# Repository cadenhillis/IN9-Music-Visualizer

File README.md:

# IN9-Music-Visualizer
Teensy 3.6  Based Music Visualizer utilizing the built-in audio library

11 IN9 Nixie tubes are driven thru low side BJT current sinks. Controllable thru the Teensy's PWM and powerful Audio Library.

The 12-150V boost supply is no laughing matter, by far the hardest to design -- as 11 IN9's can draw a peak of 20W. The medium power and high-voltage are quite a challenge for any electronics hobbiest.

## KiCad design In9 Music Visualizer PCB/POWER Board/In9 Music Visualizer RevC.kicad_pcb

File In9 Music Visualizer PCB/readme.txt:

This top level KiCad project is the top-level schematic with the board.

The Power Board and Signal Board sub directorys are boards separated by their sections, as the power side works better with 2oz 4 layers and the signal side only needs 2 layers and 2oz is overkill

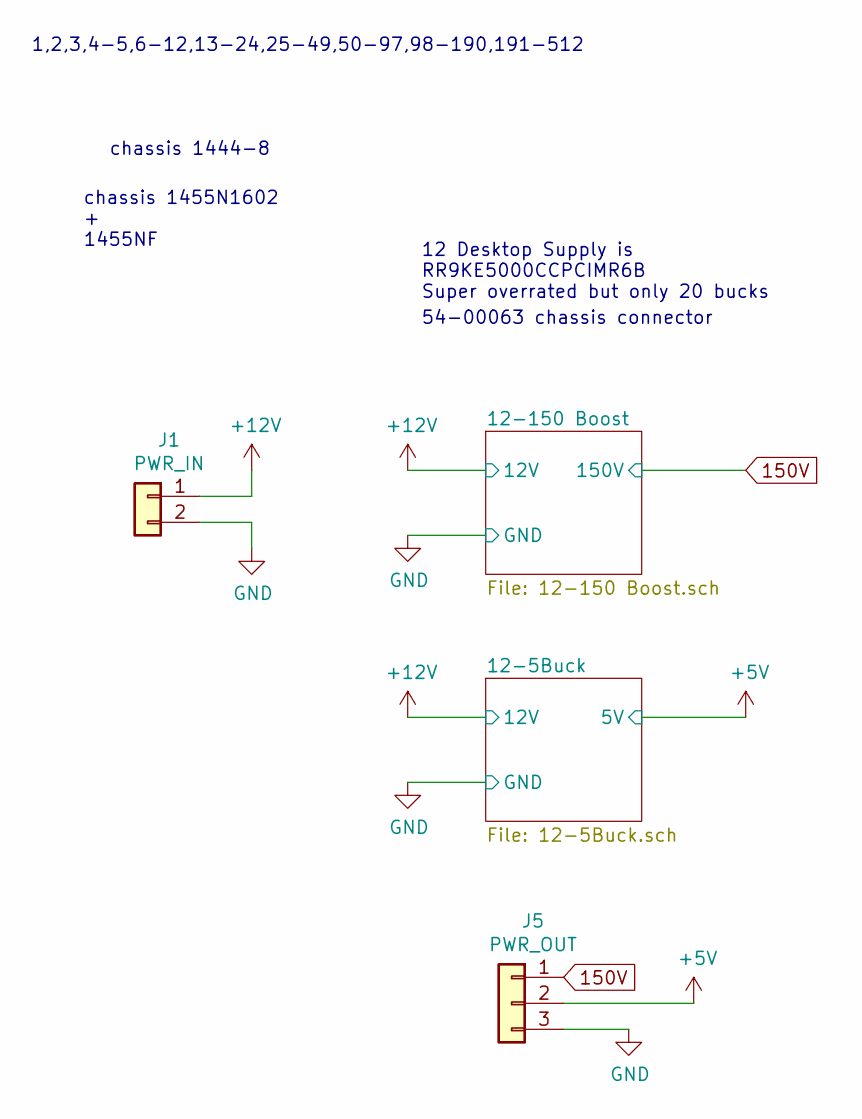
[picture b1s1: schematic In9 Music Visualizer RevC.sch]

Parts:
J1: PWR_IN; 640456-2
J5: PWR_OUT; 640456-3

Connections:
150V: J5.1; also elsewhere on the board
+5V: J5.2; also elsewhere on the board
+12V: J1.1; also elsewhere on the board
GND: J1.2, J5.3; also elsewhere on the board

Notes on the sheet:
chassis 1455N1602 + 1455NF
chassis 1444-8
54-00063 chassis connector
1,2,3,4-5,6-12,13-24,25-49,50-97,98-190,191-512
12 Desktop Supply is RR9KE5000CCPCIMR6B Super overrated but only 20 bucks

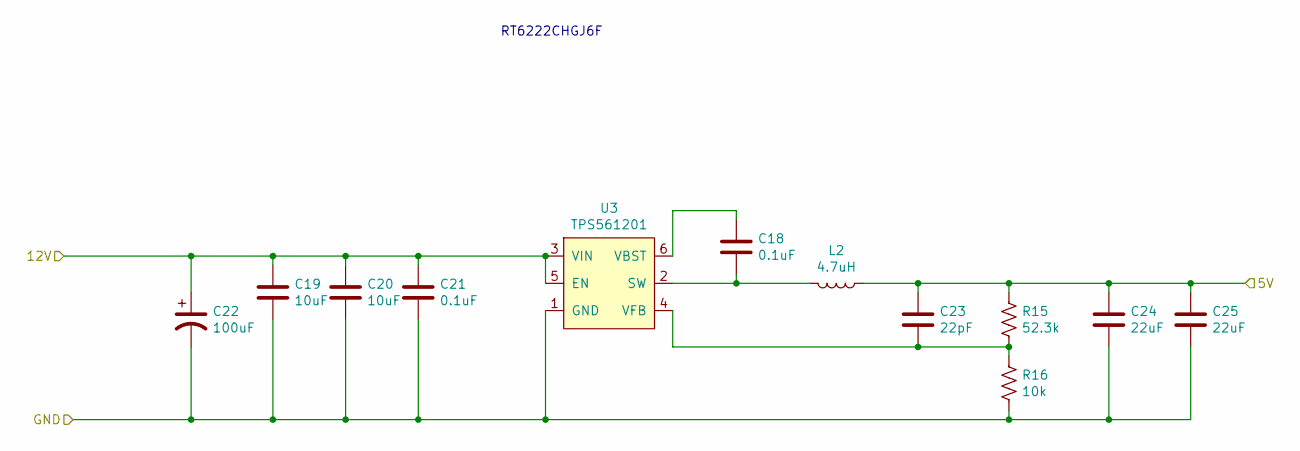
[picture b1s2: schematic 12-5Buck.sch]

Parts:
C18, C21: 0.1uF; C_0805_2012Metric_Pad1.18x1.45mm_HandSolder
C19, C20: 10uF; C_0805_2012Metric_Pad1.18x1.45mm_HandSolder
C22: 100uF; CP_Radial_D6.3mm_P2.50mm
C23: 22pF; C_0805_2012Metric_Pad1.18x1.45mm_HandSolder
C24, C25: 22uF; C_0805_2012Metric_Pad1.18x1.45mm_HandSolder
L2: 4.7uH; L_Bourns_SRN6045TA
R15: 52.3k; R_0805_2012Metric_Pad1.20x1.40mm_HandSolder
R16: 10k; R_0805_2012Metric_Pad1.20x1.40mm_HandSolder
U3: TPS561201; SOT-23-6

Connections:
+5V: C23.1, C24.1, C25.1, L2.1, R15.1; also elsewhere on the board
+12V: C19.1, C20.1, C21.1, C22.1, U3.3 (VIN), U3.5 (EN); also elsewhere on the board
GND: C19.2, C20.2, C21.2, C22.2, C24.2, C25.2, R16.2, U3.1 (GND); also elsewhere on the board
unnamed: C18.1, U3.6 (VBST)
unnamed: C18.2, L2.2, U3.2 (SW)
unnamed: C23.2, R15.2, R16.1, U3.4 (VFB)

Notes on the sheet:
RT6222CHGJ6F

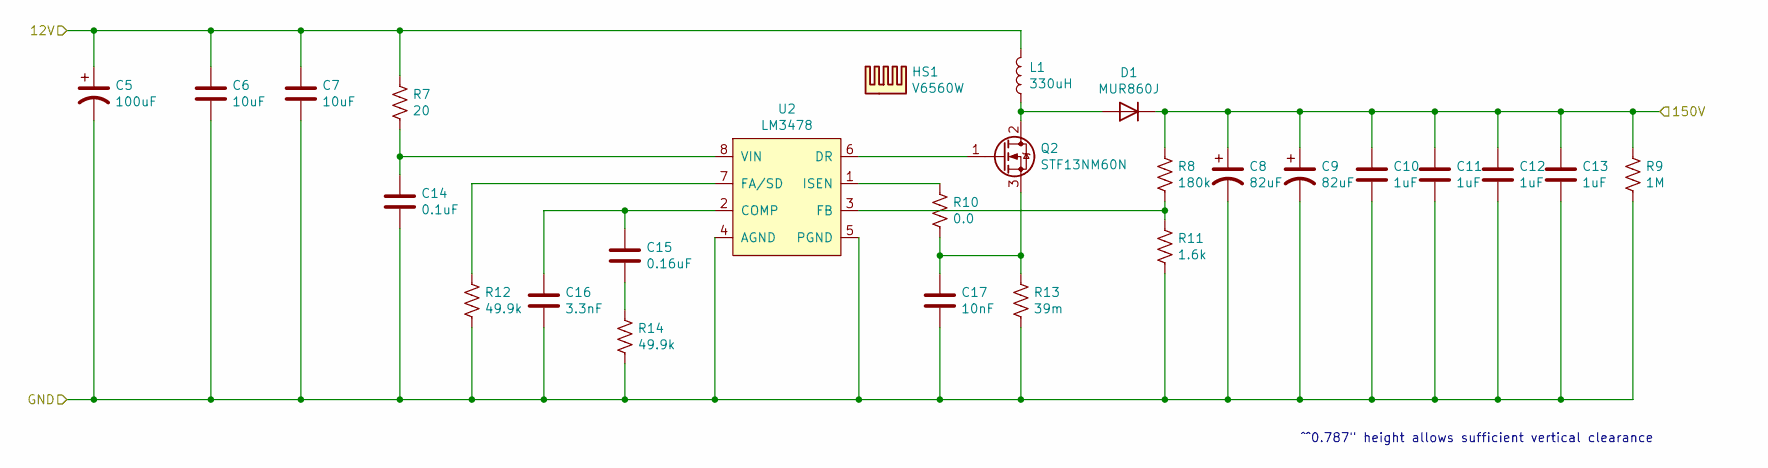
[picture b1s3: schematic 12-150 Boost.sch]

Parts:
C5: 100uF; CP_Radial_D6.3mm_P2.50mm
C6, C7: 10uF; C_0805_2012Metric_Pad1.18x1.45mm_HandSolder
C8, C9: 82uF; CP_Radial_D18.0mm_P7.50mm
C10, C11, C12, C13: 1uF; C_2220_5650Metric_Pad1.97x5.40mm_HandSolder
C14: 0.1uF; C_0805_2012Metric_Pad1.18x1.45mm_HandSolder
C15: 0.16uF; C_0805_2012Metric_Pad1.18x1.45mm_HandSolder
C16: 3.3nF; C_0805_2012Metric_Pad1.18x1.45mm_HandSolder
C17: 10nF; C_0805_2012Metric_Pad1.18x1.45mm_HandSolder
D1: MUR860J; D_SMC_Handsoldering
HS1: V6560W
L1: 330uH; L_Murata_6000B
Q2: STF13NM60N; TO-220-3_Vertical
R7: 20; R_0805_2012Metric_Pad1.20x1.40mm_HandSolder
R8: 180k; R_0805_2012Metric_Pad1.20x1.40mm_HandSolder
R9: 1M; R_0805_2012Metric_Pad1.20x1.40mm_HandSolder
R10: 0.0; R_0805_2012Metric_Pad1.20x1.40mm_HandSolder
R11: 1.6k; R_0805_2012Metric_Pad1.20x1.40mm_HandSolder
R12, R14: 49.9k; R_0805_2012Metric_Pad1.20x1.40mm_HandSolder
R13: 39m; R_1206_3216Metric_Pad1.30x1.75mm_HandSolder
U2: LM3478; SO-8_3.9x4.9mm_P1.27mm

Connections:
150V: C8.1, C9.1, C10.1, C11.1, C12.1, C13.1, D1.1 (K), R8.1, R9.1; also elsewhere on the board
+12V: C5.1, C6.1, C7.1, L1.2, R7.1; also elsewhere on the board
GND: C5.2, C6.2, C7.2, C8.2, C9.2, C10.2, C11.2, C12.2, C13.2, C14.2, C16.2, C17.2, R9.2, R11.2, R12.2, R13.2, R14.2, U2.4 (AGND), U2.5 (PGND); also elsewhere on the board
unnamed: C14.1, R7.2, U2.8 (VIN)
unnamed: C15.1, C16.1, U2.2 (COMP)
unnamed: C15.2, R14.1
unnamed: C17.1, Q2.3 (S), R10.1, R13.1
unnamed: D1.2 (A), L1.1, Q2.2 (D)
unnamed: Q2.1 (G), U2.6 (DR)
unnamed: R10.2, U2.1 (ISEN)
unnamed: R8.2, R11.1, U2.3 (FB)
unnamed: R12.1, U2.7 (FA/SD)

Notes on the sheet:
^^0.787" height allows sufficient vertical clearance

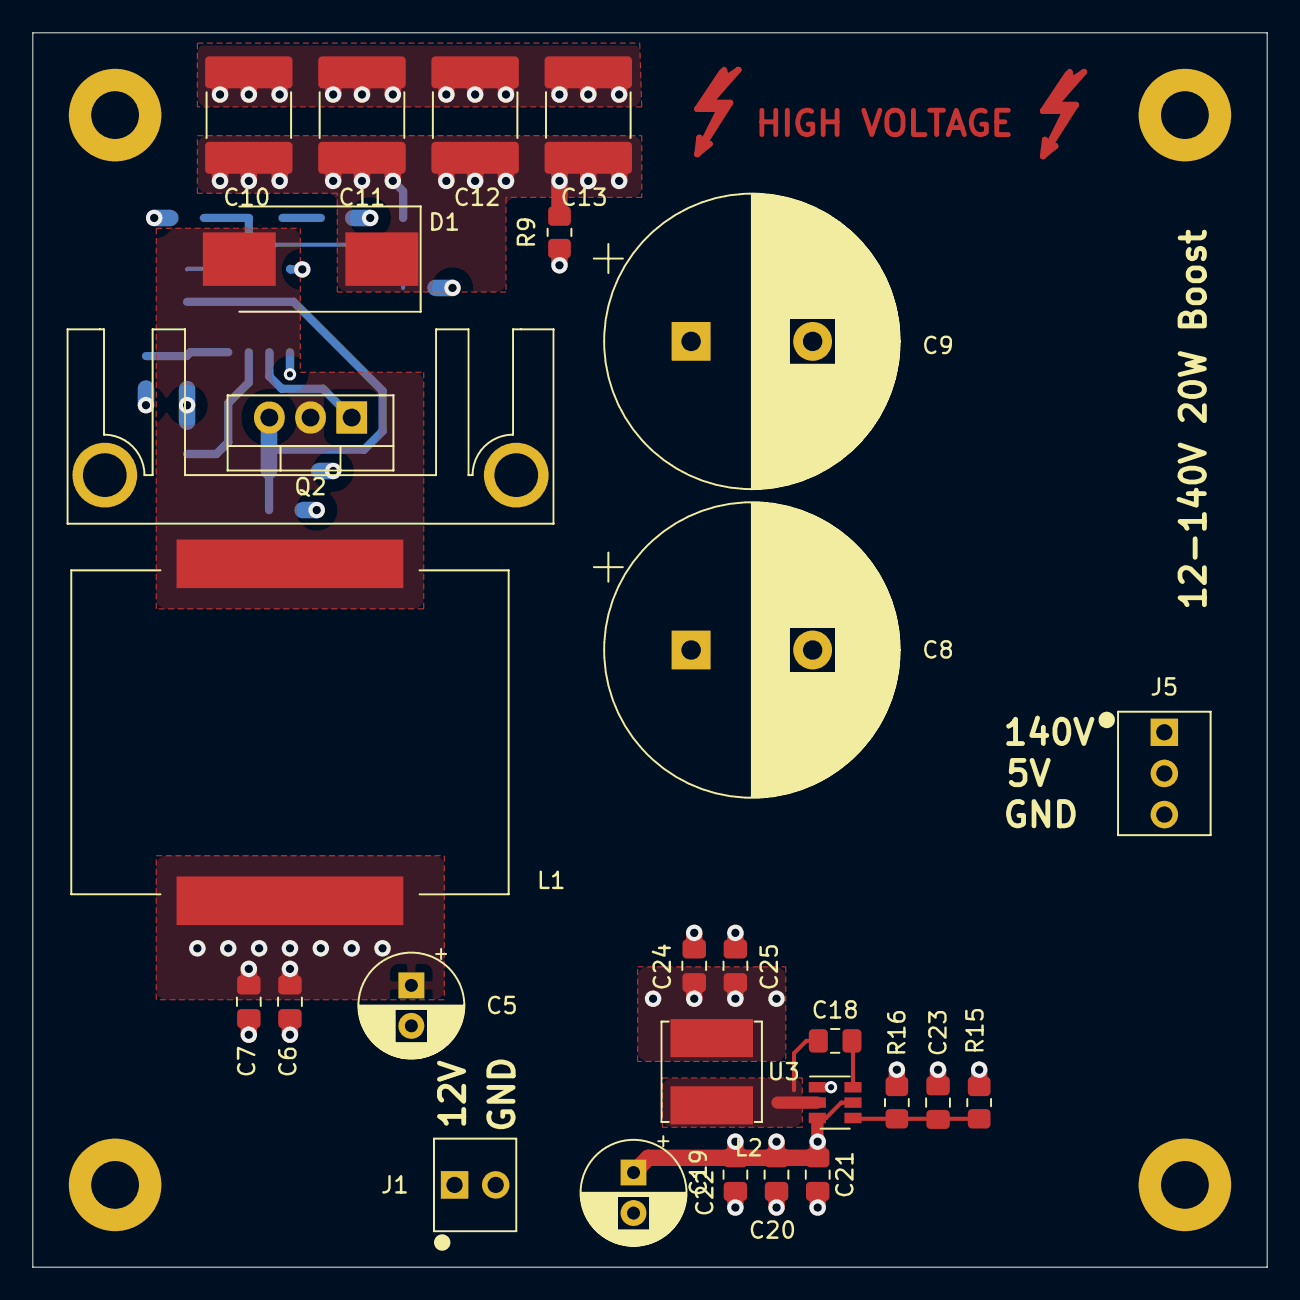
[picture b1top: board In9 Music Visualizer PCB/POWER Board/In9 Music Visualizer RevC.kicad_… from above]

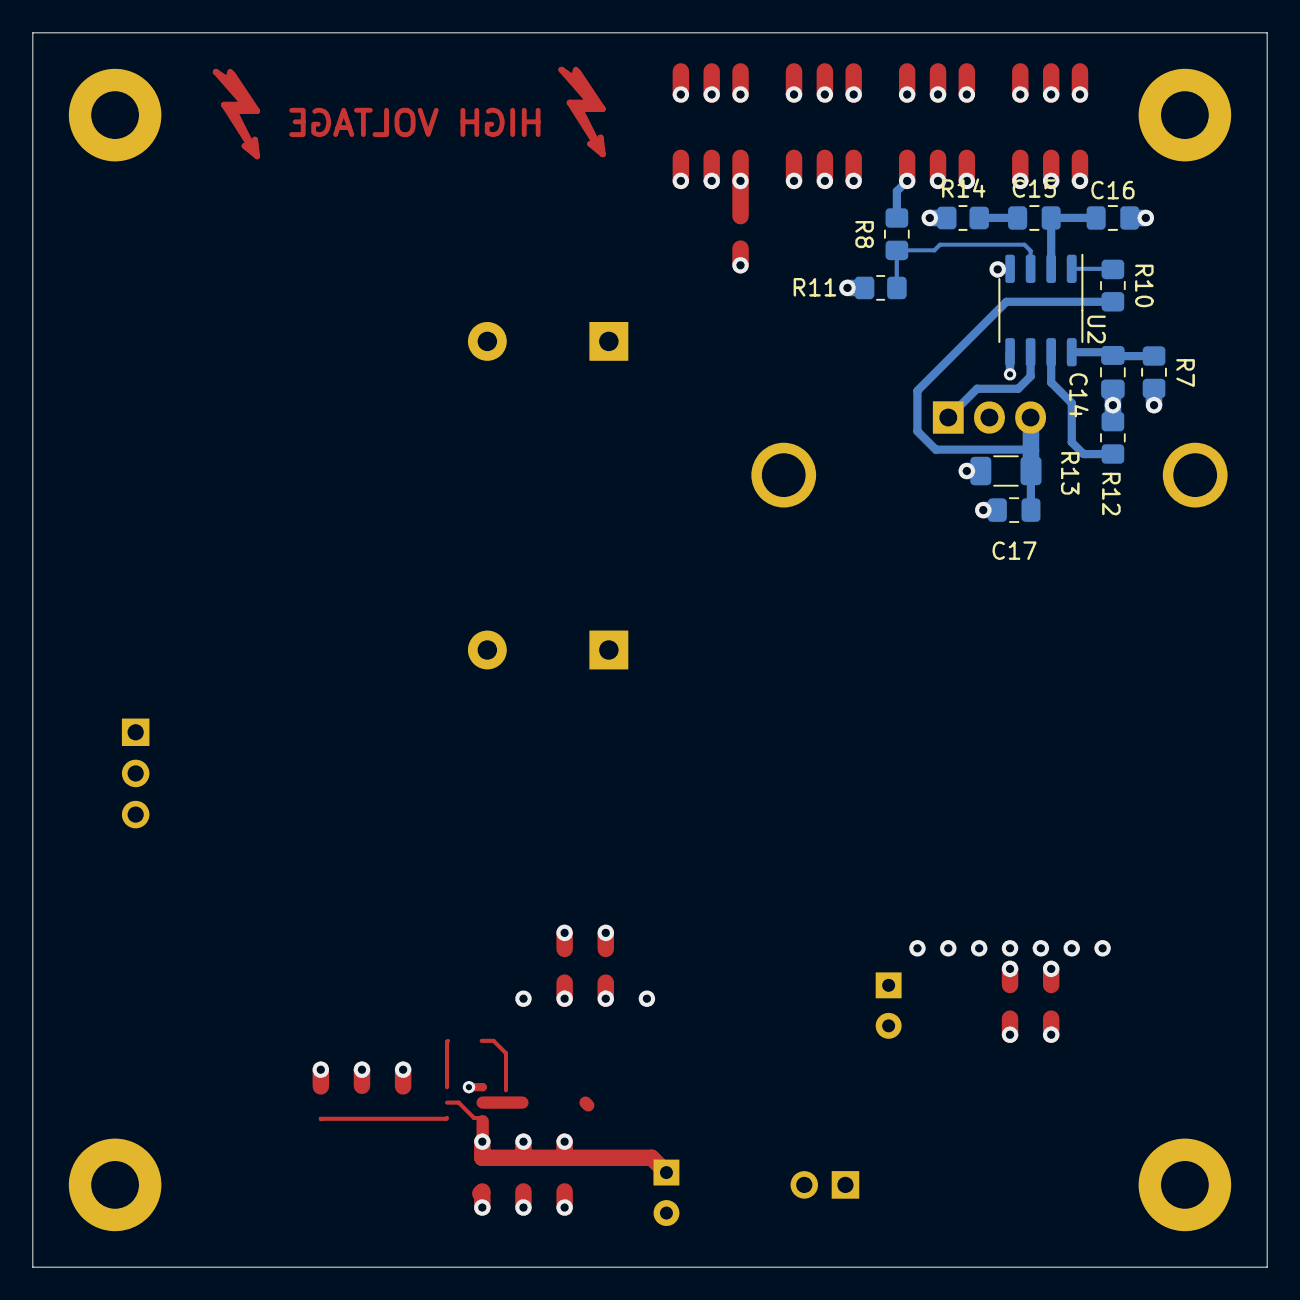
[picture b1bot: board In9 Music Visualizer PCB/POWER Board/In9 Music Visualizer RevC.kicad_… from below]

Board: 4 copper layers, 76.2 x 76.2 mm, 40 parts (12 on the bottom side), 16 nets.

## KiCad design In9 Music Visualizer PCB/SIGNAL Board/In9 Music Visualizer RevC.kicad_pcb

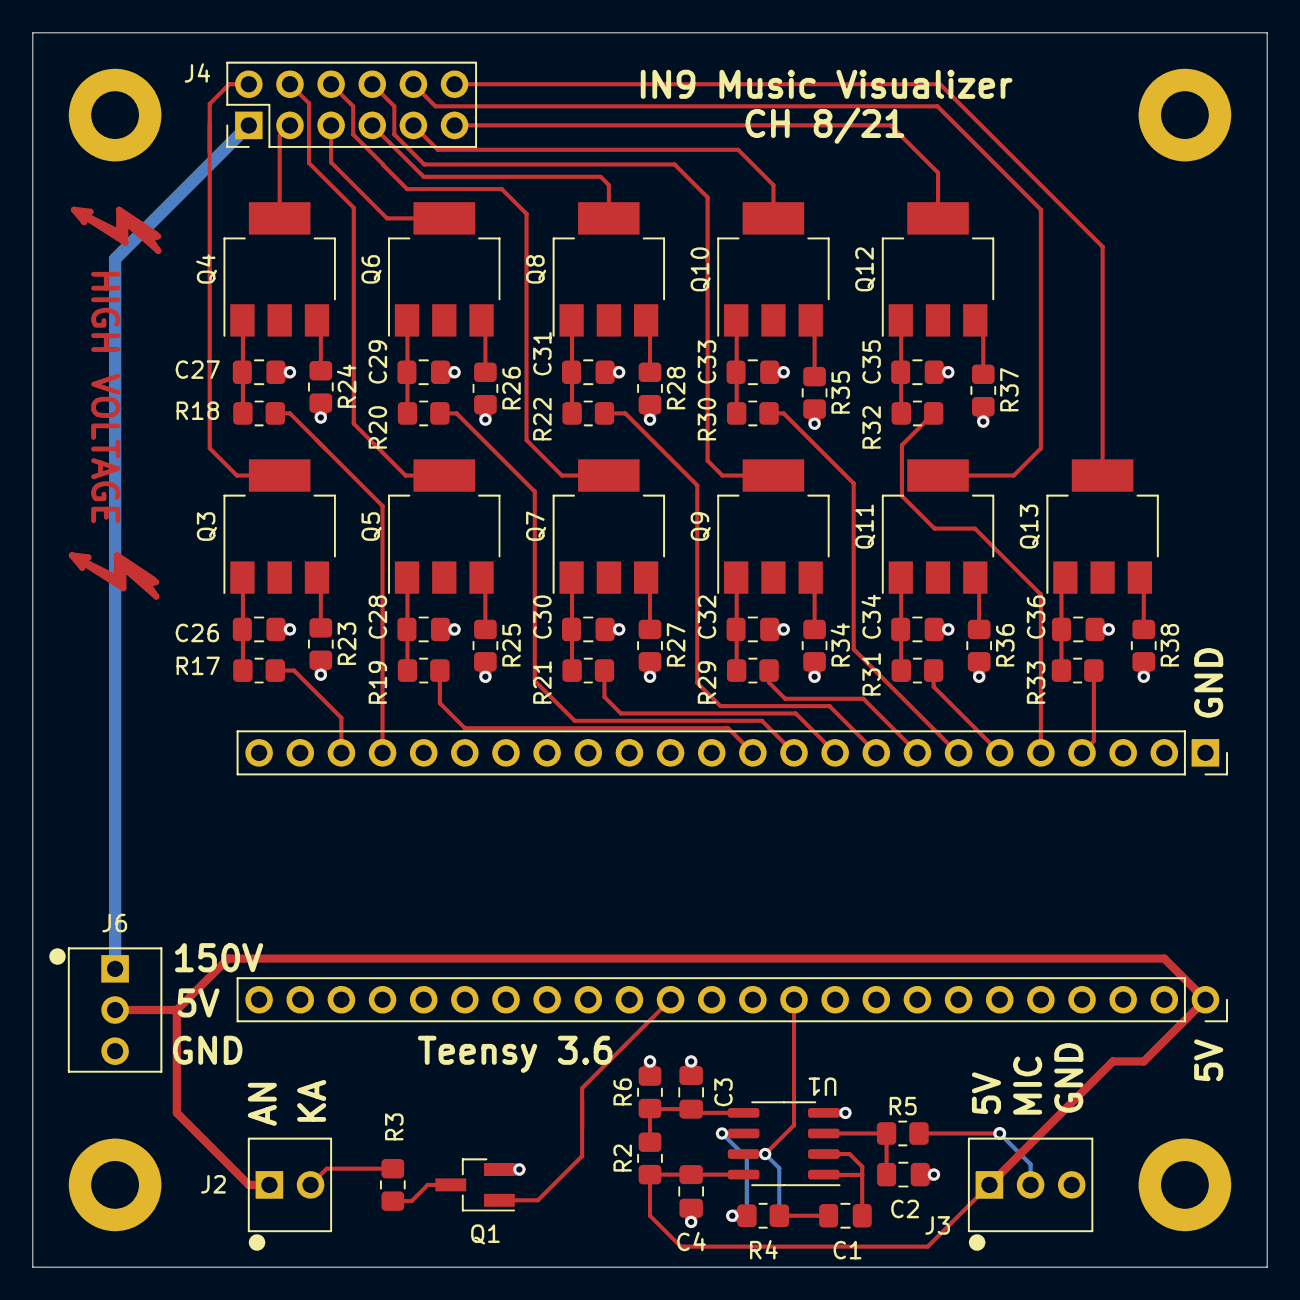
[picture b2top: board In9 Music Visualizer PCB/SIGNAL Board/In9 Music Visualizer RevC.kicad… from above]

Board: 2 copper layers, 76.2 x 76.2 mm, 61 parts (1 on the bottom side), 57 nets.

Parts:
C1, C3, C4: 0.1uF; C_0805_2012Metric_Pad1.18x1.45mm_HandSolder
C2: 620pF; C_0805_2012Metric_Pad1.18x1.45mm_HandSolder
C26, C27, C28, C29, C30, C31, C32, C33, C34, C35, C36: 4.7uF; C_0805_2012Metric_Pad1.18x1.45mm_HandSolder
J2: PWR_IN; 640456-2
J3: MIC_INPUT; 640456-3
J4: IN9_MOUNTING_BOARD; PinHeader_2x06_P2.54mm_Vertical
J6: PWR_IN; 640456-3
MCU1: Teensy 3.6; Teensy3.6
Q1: DMN6140L-13; SOT-23_Handsoldering
Q3, Q4, Q5, Q6, Q7, Q8, Q9, Q10, Q11, Q12, Q13: FZT857TA; SOT-223-3_TabPin2
R1, R5, R6: 10k; R_0805_2012Metric_Pad1.20x1.40mm_HandSolder
R2: 69.8k; R_0805_2012Metric_Pad1.20x1.40mm_HandSolder
R3: 330; R_0805_2012Metric_Pad1.20x1.40mm_HandSolder
R4: 20k; R_0805_2012Metric_Pad1.20x1.40mm_HandSolder
R17, R18, R19, R20, R21, R22, R29, R30, R31, R32, R33: 2.2k; R_0805_2012Metric_Pad1.20x1.40mm_HandSolder
R23, R24, R25, R26, R27, R28, R34, R35, R36, R37, R38: 180; R_0805_2012Metric_Pad1.20x1.40mm_HandSolder
U1: LMV358; SOIC-8_3.9x4.9mm_P1.27mm

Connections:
150V: J4.1, J6.1
+5V: C4.1, J2.1, J3.1, J6.2, MCU1.48, R2.1, U1.8
/0.625V: C3.1, R2.2, R6.1, U1.5
/ADC_in: MCU1.38, R1.1, U1.7
/MIC_out: J3.2, R5.2
/PWM_0: MCU1.22, R17.2
/PWM_1: MCU1.21, R18.2
/PWM_2: MCU1.12, R19.2
/PWM_3: MCU1.11, R20.2
/PWM_4: MCU1.10, R21.2
/PWM_5: MCU1.9, R22.2
/PWM_6: MCU1.8, R29.2
/PWM_7: MCU1.7, R30.2
/PWM_8: MCU1.6, R31.2
/PWM_9: MCU1.5, R32.2
/PWM_10: MCU1.4, R33.2
/pwr_led: MCU1.35, Q1.1
GND: C2.2, C3.2, C4.2, C26.2, C27.2, C28.2, C29.2, C30.2, C31.2, C32.2, C33.2, C34.2, C35.2, C36.2, J3.3, J6.3, MCU1.1, MCU1.34, MCU1.47, Q1.2, R6.2, R23.2, R24.2, R25.2, R26.2, R27.2, R28.2, R34.2, R35.2, R36.2, R37.2, R38.2, U1.4
unnamed: C1.1, R4.2
unnamed: C1.2, U1.1, U1.2
unnamed: C2.1, R5.1, U1.3
unnamed: C26.1, Q3.1, R17.1
unnamed: C27.1, Q4.1, R18.1
unnamed: C28.1, Q5.1, R19.1
unnamed: C29.1, Q6.1, R20.1
unnamed: C30.1, Q7.1, R21.1
unnamed: C31.1, Q8.1, R22.1
unnamed: C32.1, Q9.1, R29.1
unnamed: C33.1, Q10.1, R30.1
unnamed: C34.1, Q11.1, R31.1
unnamed: C35.1, Q12.1, R32.1
unnamed: C36.1, Q13.1, R33.1
unnamed: J2.2, R3.1
unnamed: J4.2, Q3.2
unnamed: J4.3, Q4.2
unnamed: J4.4, Q5.2
unnamed: J4.5, Q6.2
unnamed: J4.6, Q7.2
unnamed: J4.7, Q8.2
unnamed: J4.8, Q9.2
unnamed: J4.9, Q10.2
unnamed: J4.10, Q11.2
unnamed: J4.11, Q12.2
unnamed: J4.12, Q13.2
unnamed: Q1.3, R3.2
unnamed: Q3.3, R23.1
unnamed: Q4.3, R24.1
unnamed: Q5.3, R25.1
unnamed: Q6.3, R26.1
unnamed: Q7.3, R27.1
unnamed: Q8.3, R28.1
unnamed: Q9.3, R34.1
unnamed: Q10.3, R35.1
unnamed: Q11.3, R36.1
unnamed: Q12.3, R37.1
unnamed: Q13.3, R38.1
unnamed: R1.2, R4.1, U1.6

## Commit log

2022-03-17 gitignore
